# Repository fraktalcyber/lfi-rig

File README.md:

# Fraktal - Laser Fault Injection (LFI) rig

This project is Fraktal's take on building an affordable Laser Fault Injection rig that allows anyone to get started with performing laser fault injection attacks, previously left only for laboratories and research institutes with expensive equipment. With this breakthrough, we hope to inspire a new wave of research and development in hardware security.

The series of blog posts related to this repository can be read from our blog
[Part 1](https://blog.fraktal.fi/laser-fault-injection-for-the-masses-1860afde5a26),
[Part 2](https://medium.com/fraktal/laser-fault-injection-for-the-masses-part-2-b86a42fd28a1), 
[Part 3](https://medium.com/fraktal/laser-fault-injection-for-the-masses-part-3-86372a233db9)

## Contents of the repository

- **Decapping** - Instructions, guidance and methodologies for decapping chips
- **LFI** - Instructions, guidance and methodologies for Laser Fault Injection and how to get the best out of the rig
- **Other** - Various other things and source material we have created and come across
- **PCB** - KiCAD project, schematic and board files for the XY2-100 driver board
- **rigv2** - 2nd generation rig using off-the-shelf xTool F1 laser engraver
- **src** - Micropython script including the XY2-100 software driver and control for the laser PWM, beam pattern visualizer

## UPDATE
Rigv2 using off-the-shelf xTool F1 laser engraver. A bit more money but a lot less hassle. Read the details from [rigv2](/rigv2/README.md)

## Chip Decapping
**The rig is capable of decapping chips!** This capability drastically simplifies the decapping process, as you can decap and then immediately move on to glitching the chip — no need to switch between different equipment or complicated setups. Read more from [decapping](https://github.com/fraktalcyber/lfi-rig/blob/main/Decapping/README.md)

## WARNING

**Before attempting to build and use this rig, please be aware that the 1064nm IR laser is invisible to the eye and extremely dangerous. As the rig is running high powered lasers even a reflected beam can cause immediate severe eye damage.** 

It is imperative to wear laser safety goggles that filter out 1064nm light and to operate the rig in a secure, enclosed box. Line the box with aluminum foil or similar materials to ensure the IR light cannot penetrate. Safety should always be your top priority as any damage to your sight is likely going to be permanent. Also be aware of the potential fire hazards as a powerful IR laser will easily burn through even thin metal.

When buying goggles, get them from reputable sources that provide some certification or other documentation so you can be sure the glasses actually filter the wavelengths. [Example from Farnell](https://fi.farnell.com/imatronic/1900-08-000/laser-safety-glasses-870-1085nm/dp/2334333)

**If you decide to decap chips with the rig here are some additional warnings.**

Ensure you have adequate fume extraction as the fumes emitted from the burning epoxy, fillers and additives in the coating can be very toxic to inhale. We are performing this in a sealed enclosure with Weller fume extractor that has active carbon filter. 

Fire hazards, as you are giving laser treatment for the epoxy, even though it has flame retardants, there is still a risk of combustion. Never leave the rig without supervision when doing this and have fire extinguisher at hand just in case.

## Shopping list

This details the main components needed to build the rig. The bill of materials for the XY2-100 driver board is listed in the README.md under the PCB folder.

- **Galvanometer (Galvo scanner):** Any that uses XY2–100 protocol and has 1064nm IR coating on the mirrors will do.  These can be had from AliExpress from various sellers for around 130 €, prices seem to vary wildly between sellers and days. If it has a DB-25 connector it likely works with our driver board directly
- **1064nm F-Theta lens:** The smaller the scan area / focus length, the higher the precision. Around 50 €.
- **1064nm IR Laser light source:** Any with at least 200 mW of optical power. The more powerful laser you have the faster you can run the rig. We started with a 200mW module which we were able to haggle to around 50 € from Alibaba but eventually settled for an off-the-shelf Sculpfun IR-2, 2W IR laser module which has integrated driver and enough power to run the rig as fast as the mirrors can move. We managed to get the IR-2 module from a campaign in Alibaba for 220 €. IR-2 is also nice because it has a red alignment laser which makes it possible to see where the laser is pointing.
- **Raspberry Pi Pico:** 5 €.
- **4 channel RS-422/485 driver:** To drive X, Y, Sync and CLK channels in XY2–100 protocol. We used Analog Devices LTC487CSW, 10 € .
- **Power supply:** Capable of providing +-15V @ 2A, we initially used a multi-channel bench power supply. For the final version we used embedded Tracopower TEN60–2423N supply which is 97 € but makes it possible to have everything in a single PCB.

## Assembly and setup

After obtaining all of the required items from the shopping list (and optionally built the driver board all you have left is to assemble the thing. If you went with the Sculpfun IR-2 laser this step is pretty straight forward.

### Mounting the laser to the Galvanometer

Mount the laser to the hole in the galvanometer. You can build proper brackets or just duct tape it together like we have. Both work equally well. Whatever you do, leave things a bit loose for now so that it is possible to align the beam to the center of the hole when you power the rig on.

### Attaching the lens

Screw in the F-Theta lens. Before attaching the lens, make sure the mirrors and the lens are clean and don't have any dust particles or other dirt as that will be likely burnt to the mirror surface when you first time power on the laser.

### Holding the rig in place

We are holding the rig in place in our lab simply with a monitor mount that can be height adjusted and which has VESA mount that can be tilted 90 degrees. The VESA mount has two L-Brackets attached to it that hold the rig in place.

### Assembling the driver PCB

The driver PCB has very few parts and is pretty straight forward to assemble. There are only few things that should be considered.

- Although the Raspberry Pi Pico can be mounted flush on the PCB we suggest mounting a pin header to the holes and then pressing the Pico in. This has benefits, it leaves a bit more clearance under the Pico and fits even the bulkiest Micro USB cables, it allows to use the pads to mount wires and additional headers for monitoring etc. We are for example driving the target chip power often straight from the Pico as this makes wiring a bit simpler. For this we have added few extra headers for select pins.
- **DB-15 Header should be mounted to the backside of the PCB**, with the rest of the components on the frontside where the Raspberry Pi Pico is.
- The PCB BOM is listed with more detail underneath the PCB folder

### Connecting all the cables and wiring pinouts

Most of the available galvanometers seem to be using similar structure and come with DB-25 connector in the galvanometer itself. It is still worth to check that the one you are planning on buying has same or similar pinout to what we used if you are planning on running our driver board.

These galvanometers come with wiring harness that has DB-25 that goes to the galvanometer with the other end having DB-15 and four loose cables. The DB-15 connector is used for the XY2-100 four channels and you can verify the pinout by beeping the cable with a multimeter in continuity mode. DB-15 should work directly with our driver and can be connected straight to the PCB.

*As we didn't want to run the rig from mains with insufficient protections, We ditched the power supply that came with the galvanometer as that connects straight to mains and doesn't offer same amount of protections as a lab power supply can provide.*

The four loose cables we had in our harness were coloured blue (-15VDC), black (GND), red (+15VDC) and yellow (Mains Earth **DO NOT CONNECT THIS UNLESS YOU KNOW WHAT YOU ARE DOING**). Blue, black and red wires can be connected to the Galvo OUT header on the driver PCB.

If you are running the Sculpfun IR-2 laser, the laser probably came with this type of connector.

The pinout for the connector is from left to right, 1kHZ PWM signal @ 3V3, GND, +24VDC

When connecting the PWM signal to the respective header on the driver PCB, it is **highly recommended to add a mechanical switch on the signal wire** this allows you to have a mechanical safety switch and prevent accidental running of the laser main beam. Only toggle the switch when everything is enclosed and you are wearing your goggles.

With everything connected it is time for test run!

### Testing the rig works and aligning the laser

With everything connected and setup the first thing you should do is to align the laser. If you went with Sculpfun IR-2, you can power the laser **with PWM signal disconnected**. This should give you a red laser spot that is the alignment beam that is firing **when the main beam is not firing**. The alignment beam spotsize is much larger than the actual IR laser spot but it can be used to align the laser horizontally and vertically to make the spot as small as possible. We haven't felt a need to do anything but an alignment visually when it looks the smallest. That has been sufficient as the rest can be compensated with software parameters.

In order to get the laser pointing through the F-Theta lens, you also need to power on the galvanometer. When giving the galvanometer -15VDC and +15VDC it centers the mirrors into zero position and makes sure that your laser spot actually goes through the lens. 

Move the laser in its mount so that it is roughly in the center of the input hole, and the laser comes through as middle of the lens as possible. Once the laser is centered, tighten all of the screws or duct tape the laser in place.

Then adjust the horizontal alignment of the whole rig by moving it up and down in the rig mount and try to get as small beam as possible.

We are running IR-2 without the collimator lens that came with the laser as we have found that it makes it easier to mount the laser flush with the galvanometer. You should try it with and without and move the laser horizontally as well to find what works best for your setup and the selected F-Theta lens. Each setup is slightly different so there are no direct guides how to get the smallest spot size on your specific setup.

After the laser is aligned and as small as possible it is time to test the mirrors move and can be controlled. To do this, **still with the PWM signal disconnect** run the findPerimeter function with parameters (x-axis start position, x-axis end position, y-axis start position, y-axis end position, time to sleep before running the perimeter) so for example

	findPerimeter(0,3500,0,3500,0)

This should draw a square with the scanning laser on whatever surface you have underneath the laser. If you can't see a uniform sized square, the mirrors don't move fluently, if you see laser points outside of the square or anything else. You need to do some debugging and figure out what is wrong.

If you on the other hand see a square, now you can use the square to align the laser rig and check that it is not tilted. We have found best to have some uniform known sized square that you use as a reference such as graph paper. Align the x and y axis in the function to get the right size and then align the rig with the graph paper on a flat surface to get the rig to be level. This is important especially if you are running the rig at full speed as slight misalignment here will mean different laser power hitting different parts of the chip. Ideally you'd want to have as uniform and flat plane as possible.

If everything works and you have everything setup now its time to try on some actual samples.

## Running the rig in fault injection mode

Provided that you managed to get everything working and setup, and have a decapped IC using our method or any other method. It is time to run the rig in fault injection mode.

You should start with mounting the sample underneath the rig as center as possible and adjusting the perimeter size using the findPerimeter function. When adjusting the perimeter, it is a good idea to go slightly over the actual die, that way you will not be missing the edges of the die which may or may not have something that causes faults. Having the sample as center as possible makes the lens work the best and keeps the spot as uniform as possible.

With the perimeter setup and parameters found it is time to put the rig inside a box, enclosure and shield your eyes with the glasses. What we have done is to add a webcam or some camera inside the box to be able to see what is happening. With most webcams it is also possible to see a faint violet tint when the IR laser main beam is firing, similar to what you can see when you view your TV remote using your phone camera.

The main function to be used for scanning the die to produce faults is scanChip.

	scanChip(0,3500,0,3500,40,True)
	
The function takes as parameters the chip perimeter and the "hop" or how much the mirrors are to be moved with a single drive cycle, the last value is True/False if the laser should be firing or not. For a test run we suggest running the scanChip with laser turned off and only the alignment beam lit, this allows you to see the scanning is working properly and that you are scanning the entire die area.

If the dry run works it is time to run with the main beam. If using the IR-2 laser a suggested starting point value for power is 8000 for the duty cycle. This has in our experiments been a nice baseline as (depending on the hopsize, thus the mirror speed) it has been enough power to cause faults to appear in most of the chips we have tried.

It is always best to start with a chip where you have full control, via a debugger or running a software loop that you know what it is doing.. We did initial tests with having a same chip as our target chip was, and run a sample firmware that runs in while true loop and just prints incrementing number into UART. Then we adjusted first the power level to something where we start seeing faults happen. Then we played around with the hop parameter and adjusting the power so that we can run the rig as fast as possible while still producing same or similar faults as initially observed.

Now the rig and parameter should be setup for trying the rig with an actual target chip and to try and for example bypass code readout protections or secure boot verifications. 

**ENJOY!**

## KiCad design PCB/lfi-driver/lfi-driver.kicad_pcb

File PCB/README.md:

# XY2-100 driver board

This file contains remarks, notes and various things regarding the driver board and its assembly.

## Bill of materials

- **R1 & R2** - 1k Ohm 0603 resistor
- **R3** - 0 Ohm 0603 jumper
- **R4-R7** - 120 Ohm 0603 terminating resistors for the XY2-100 channels
- **J1** - Terminal Block, Metz Connect Type059 RT06303HBWC 1x3
- **J2 & J3** - Terminal Block, Metz Connect  Type059 RT06302HBWC 1x2
- **J4** - DB15 connector
- **PSU** - Traco Power TEN60-2423N, embedded power supply
- **U1** - Raspberry Pi Pico
- **U2** - LTC487CSW, 4 channel RS422/485 differential driver

## Remarks

- DB15 connector should be mounted on the opposite side of the PCB.
- Raspberry Pi Pico should be mounted on a pin header to allow for more cleareance under the USB cable

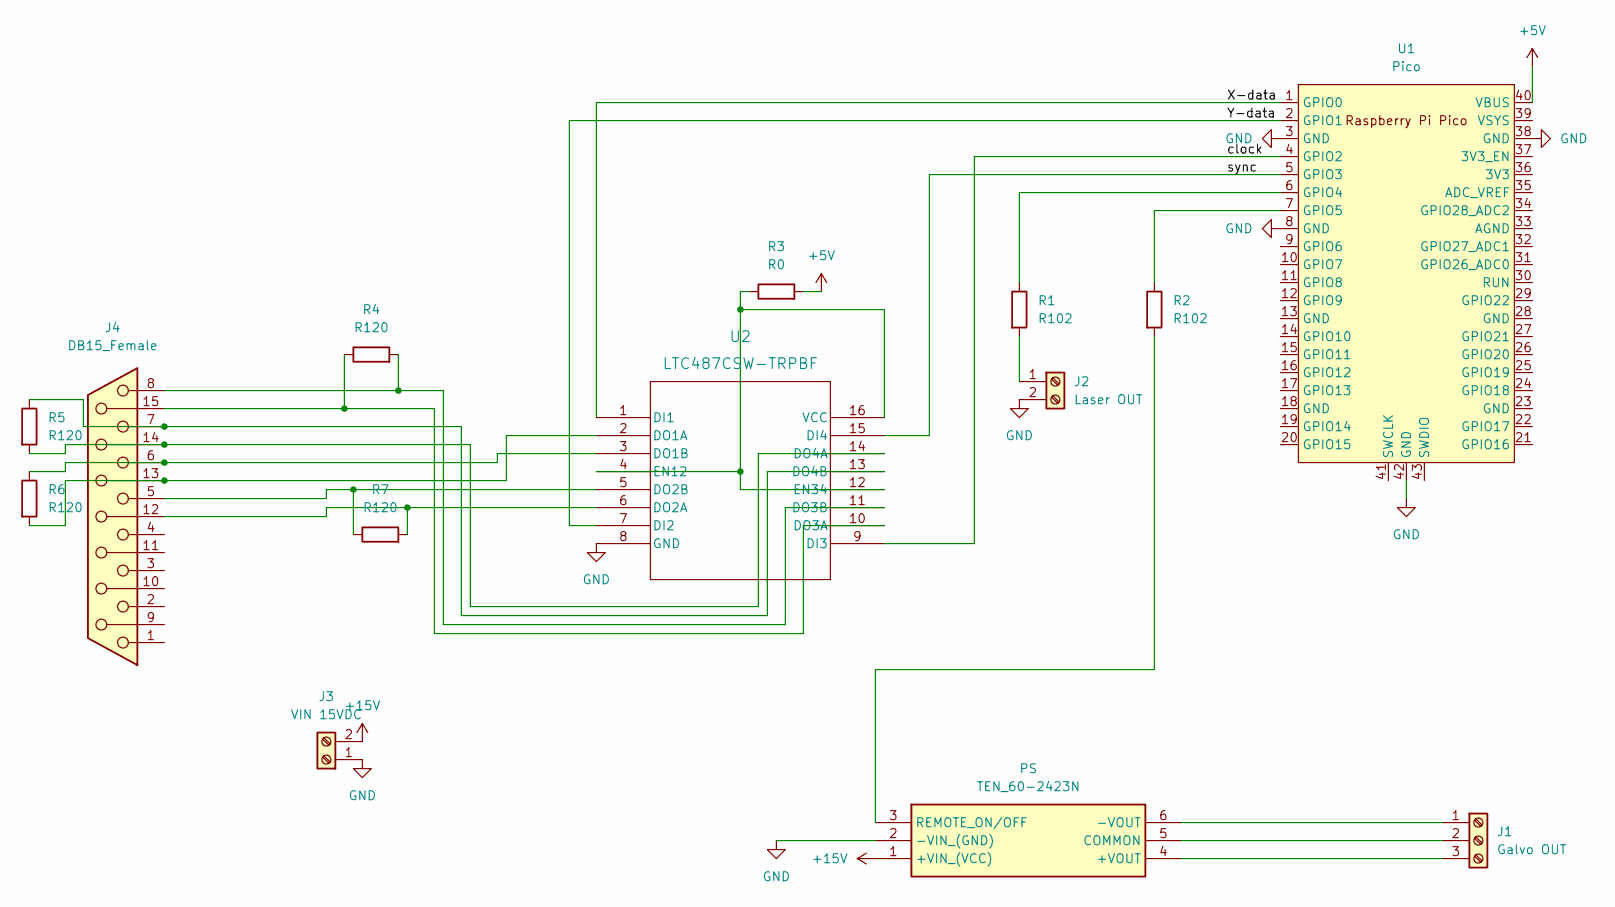
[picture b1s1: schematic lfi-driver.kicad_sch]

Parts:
J1: Galvo OUT; TerminalBlock_MetzConnect_Type059_RT06303HBWC_1x03_P3.50mm_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
J2: Laser OUT; TerminalBlock_MetzConnect_Type059_RT06302HBWC_1x02_P3.50mm_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
J3: VIN 15VDC; TerminalBlock_MetzConnect_Type059_RT06302HBWC_1x02_P3.50mm_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
J4: DB15_Female; DSUB-15_Female_Vertical_P2.77x2.84mm
PSU1: TEN_60-2423N; TEN602423N; Manufacturer_Part_Number TEN 60-2423N
R1, R2: R102; R_0603_1608Metric_Pad0.98x0.95mm_HandSolder
R3: R0; R_0603_1608Metric_Pad0.98x0.95mm_HandSolder
R4, R5, R6, R7: R120; R_0603_1608Metric_Pad0.98x0.95mm_HandSolder
U1: Pico; RPi_Pico_SMD_TH
U2: LTC487CSW-TRPBF; SO-16_SW_LIT

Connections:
+5V: R3.2, U1.40 (VBUS)
+15V: J3.2, PSU1.1 (+VIN_(VCC)); also elsewhere on the board
/X-data: U1.1 (GPIO0), U2.1 (DI1)
/Y-data: U1.2 (GPIO1), U2.7 (DI2)
/clock: U1.4 (GPIO2), U2.9 (DI3)
/sync: U1.5 (GPIO3), U2.15 (DI4)
GND: J2.2, J3.1, PSU1.2 (-VIN_(GND)), U1.3 (GND), U1.8 (GND), U1.38 (GND), U1.42 (GND), U2.8 (GND); also elsewhere on the board
unnamed 7: J1.1, PSU1.6 (-VOUT); also elsewhere on the board
unnamed 8: J1.2, PSU1.5 (COMMON); also elsewhere on the board
unnamed 9: J1.3, PSU1.4 (+VOUT); also elsewhere on the board
unnamed: J2.1, R1.2
unnamed 11: PSU1.3 (REMOTE_ON/OFF), R2.2; also elsewhere on the board
unnamed: R1.1, U1.6 (GPIO4)
unnamed: R2.1, U1.7 (GPIO5)
unnamed: R3.1, U2.4 (EN12), U2.12 (EN34), U2.16 (VCC)
unnamed: J4.15, R4.1, U2.10 (DO3A)
unnamed: J4.8, R4.2, U2.11 (DO3B)
unnamed: J4.5, R7.1, U2.5 (DO2B)
unnamed: J4.12, R7.2, U2.6 (DO2A)
unnamed: J4.13, R6.2, U2.2 (DO1A)
unnamed: J4.6, R6.1, U2.3 (DO1B)
unnamed: J4.7, R5.1, U2.13 (DO4B)
unnamed: J4.14, R5.2, U2.14 (DO4A)

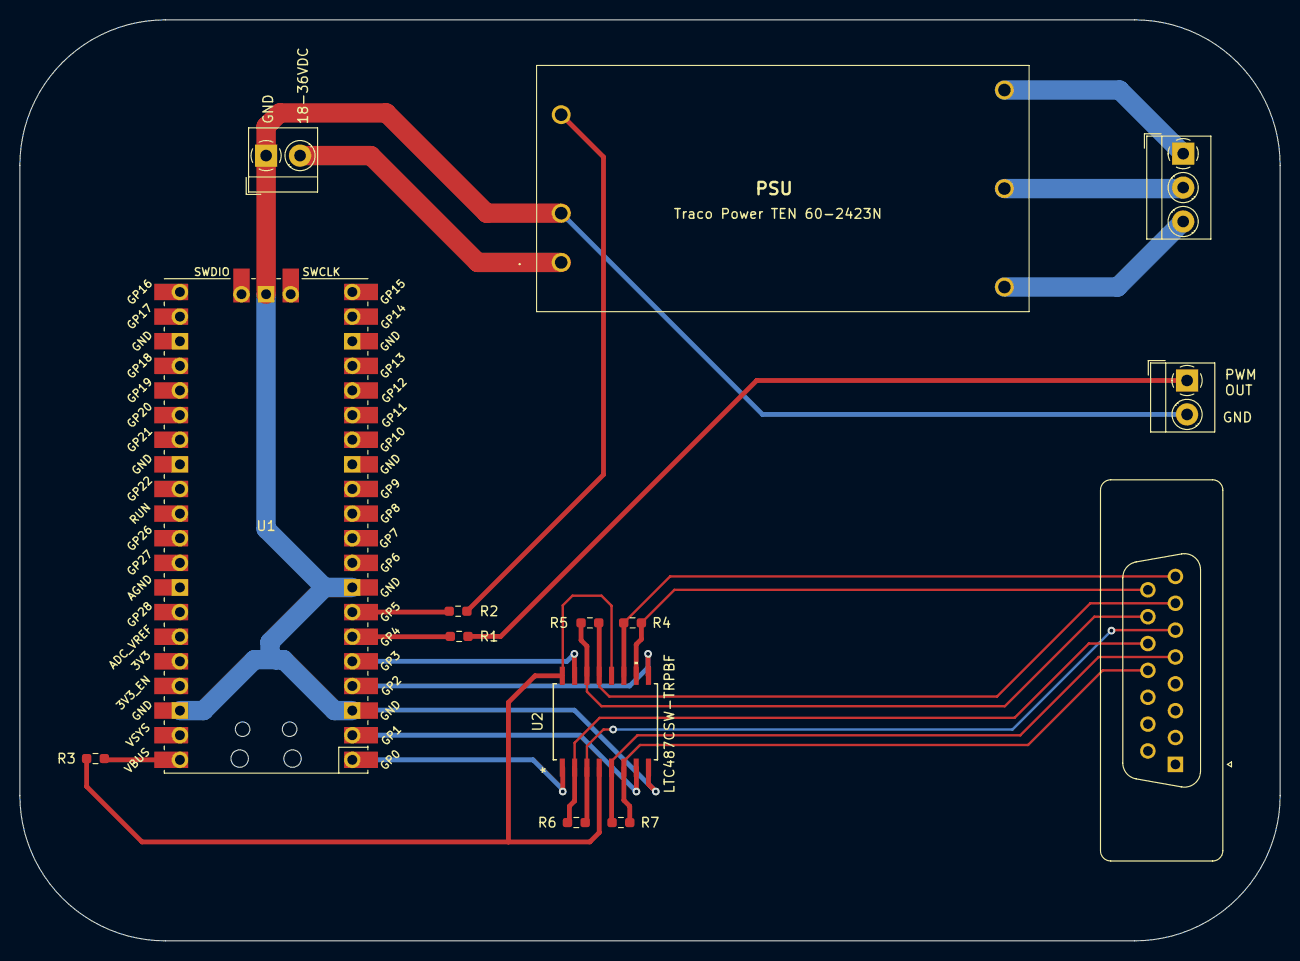
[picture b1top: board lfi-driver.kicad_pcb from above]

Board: 2 copper layers, 130.0 x 95.0 mm, 14 parts (0 on the bottom side), 23 nets.

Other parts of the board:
PSU: TEN_60-2423N; TEN602423N

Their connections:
+15V: PSU.1 (+VIN_(VCC)); also elsewhere on the board
GND: PSU.2 (-VIN_(GND)); also elsewhere on the board
unnamed 7: PSU.6 (-VOUT); also elsewhere on the board
unnamed 8: PSU.5 (COMMON); also elsewhere on the board
unnamed 9: PSU.4 (+VOUT); also elsewhere on the board
unnamed 11: PSU.3 (REMOTE_ON/OFF); also elsewhere on the board

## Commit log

2024-08-07 Initial commit for XY-Driver code and PCB designs
2024-08-08 Images for readme
2024-08-21 Helper script to visualize scan patterns
    This script will show some example scan patterns and make it easier to visualize them
2024-09-04 Edit due to error noticed in the visualization
2024-09-19 Update README.md
    Added some additional warnings regarding decapping
2024-09-19 Decapping intro added
2024-09-26 rigv2 added
2024-09-26 readability improvements
2024-10-02 appended g-code content to README.md
